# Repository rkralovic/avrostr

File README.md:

# AVR-OSTR

This project is an implementation of a turtle robot based on AVR microcontroller.

## Mechanical design

The hardware design is based on [https://www.instructables.com/OSTR/](https://www.instructables.com/OSTR/).

Mechanical parts are designed using [OpenSCAD](https://openscad.org). Running
`make` in the `mechanical` directory builds STL files suitable for 3d-printing.
The design has the following parts:

* `Chassis.scad` is the main chassis structure.
* `Caster.scad` holds a support bearing ball.
* `PenCollar.scad` holds the pen.
* `Wheel.scad` is the wheel. You need to print 2 of them

The following extra parts are needed for assembly:

* Bearing ball with diameter approx 15.875mm.
* 2x o-ring 42mm x 3mm used as tires. It is important that it fits tightly to the wheels.
* 2x battery holder for 2 AA batteries (e.g. 12BHC321A-GR).
* M3 nuts and screws (for battery holders and stepper motors).
* DIN7981 screws to fix the wheels and PCB
  ([example](https://www.conrad.ch/de/p/toolcraft-din7981-c-h-2-9c4-5-linsenblechschrauben-2-9-mm-4-5-mm-kreuzschlitz-phillips-din-7981-stahl-verzinkt-1-st-889176.html?searchType=SearchRedirect)).
* (optional) Two large nuts that can be glued to the back of the chassis for better stability.

## Electronic design

Schematics and PCB layout are provided as a Kicad project in this directory.
Component list is summarized in `bom.csv`.

## Firmware

Source of the firmware, which runs on the AVR microcontroller of the robot, is
in the directory `fw`. You need reasonable new avr-g++ in order to compile the
firmware, which uses C++20. Development was done using avr-g++ 11.2.0.

The AVR firmware can be flashed using avrdude and an UPDI-capable programmer by
running `make write`.

A smoke test is in `fw/test`. It uses simavr library to simulate the AVR code.

Note: To compile the firmware, you need to first generate the input data, see
the next section for details. Beyond that, the tests depend on simavr, gmock,
and gtest libraries.

## Image data

The image data for the robot are prepared using a tool in `gendata` directory.
Source images are in `gendata/input` in svg file format. The tool depend on
absl, cairo, xcb, cairo-pdf, and xcb-iccm libraries.

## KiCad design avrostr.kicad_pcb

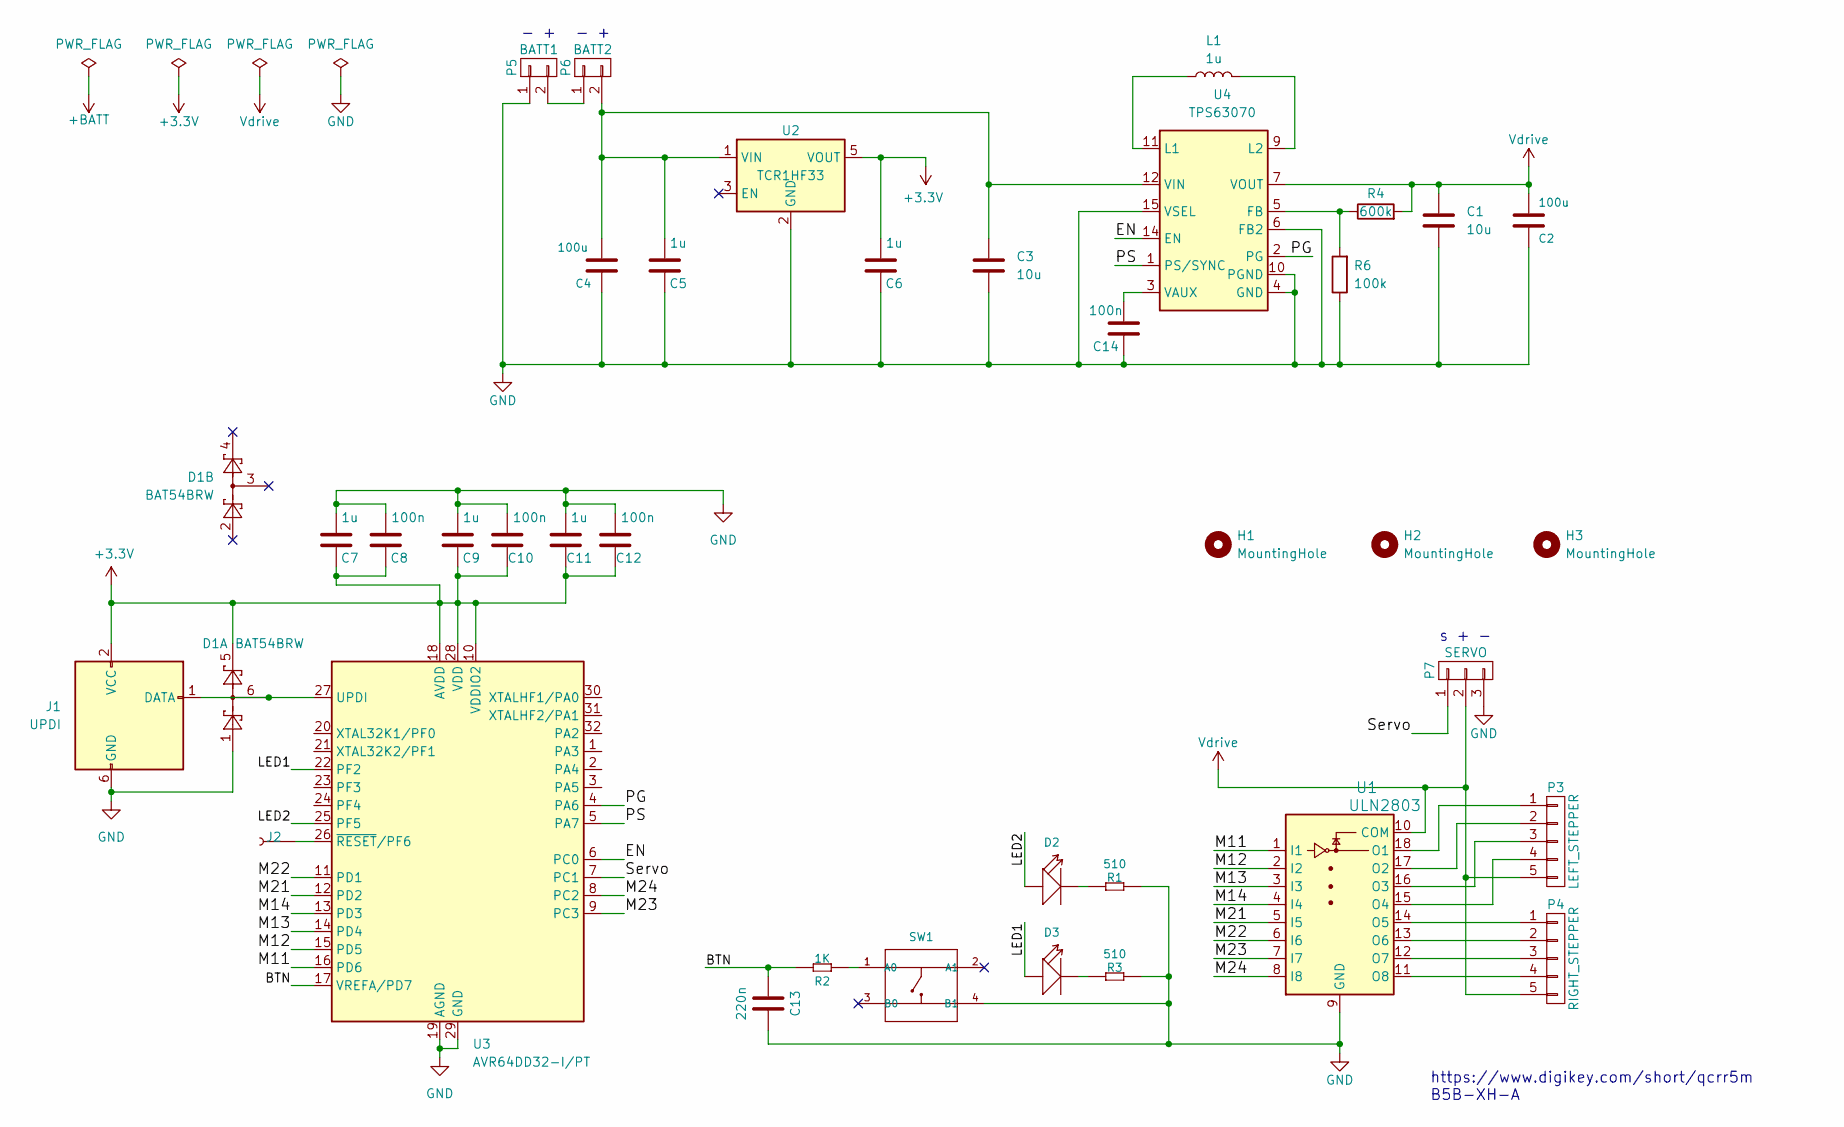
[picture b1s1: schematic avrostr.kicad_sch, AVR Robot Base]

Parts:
C1, C3: 10u; C_0402_1005Metric; Mouser 81-GRM155R61A106ME1D
C2, C4: 100u; C_1210_3225Metric; Mouser 81-GRM32ER61A107ME0K
C5, C6, C7, C9, C11: 1u; C_0402_1005Metric; Mouser 81-GRM155R61H105ME5D
C8, C10, C12, C14: 100n; C_0402_1005Metric; Mouser 81-GRM155R71H104KE4D
C13: 220n; C_0603_1608Metric; Mouser GCM188R71H224KA64
D1: BAT54BRW; SOT-363_SC-70-6; Mouser 241-BAT54BRWR100001
D2, D3: RED; LED_0603_1608Metric; Mouser 710-150060RS75000
H1, H2, H3: MountingHole; MountingHole_3.2mm_M3_ISO14580
J1: UPDI; PinHeader_2x03_P2.54mm_Vertical; Mouser 649-78511-203HLF
J2: Conn_01x01_Female; TestPoint_Pad_D1.0mm
L1: 1u; L_Coilcraft_XxL4020; Mouser XFL4020-102MEC
P3: LEFT_STEPPER; JST_B5B-XH-A; Digikey 455-2270-ND
P4: RIGHT_STEPPER; JST_B5B-XH-A; Digikey 455-2270-ND
P5: BATT1; TerminalBlock_Phoenix_PT-1,5-2-3.5-H_1x02_P3.50mm_Horizontal; Mouser 651-1984617
P6: BATT2; TerminalBlock_Phoenix_PT-1,5-2-3.5-H_1x02_P3.50mm_Horizontal; Mouser 651-1984617
P7: SERVO; Pin_Header_Straight_1x03; Digikey 1849-1003-ND
R1, R3: 510; R_0402_1005Metric; Mouser 603-RC0402FR-13510RL
R2: 1K; R_0402_1005Metric; Mouser 603-AC0402FR-071KL
R4: 600k; R_0402_1005Metric; Mouser RC0402FR-07604KL
R6: 100k; R_0402_1005Metric; Mouser 791-WR04X1003FTL
SW1: type="R" model="SMD-BUTTON_4P-5.2X5.2X1.5MM-SKQGA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; SW4-SMD-5.2X5.2X1.5MM; MPN SKQGADE010; LCSC C318889
U1: ULN2803; SOP-18_7x12.5mm_P1.27mm; Digikey 4518-ULN2803ACT-ND
U2: TCR1HF33; SOT-23-5; Mouser 757-TCR1HF33BLMCT
U3: AVR64DD32-I/PT; TQFP-32_7x7mm_P0.8mm; Digikey 150-AVR64DD32-I/PT-ND
U4: TPS63070; VQFN-15-TPS63070; Mouser 595-TPS630702RNMR

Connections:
+3.3V: C6.2, C7.1, C8.2, C9.1, C10.2, C11.1, C12.2, D1.5, J1.2 (VCC), U2.5 (VOUT), U3.10 (VDDIO2), U3.18 (AVDD), U3.28 (VDD)
/BTN: C13.1, R2.1, U3.17 (VREFA/PD7)
/EN: U3.6 (PC0), U4.14 (EN)
/LED1: D3.1 (+), U3.22 (PF2)
/LED2: D2.1 (+), U3.25 (PF5)
/M11: U1.1 (I1), U3.16 (PD6)
/M12: U1.2 (I2), U3.15 (PD5)
/M13: U1.3 (I3), U3.14 (PD4)
/M14: U1.4 (I4), U3.13 (PD3)
/M21: U1.5 (I5), U3.12 (PD2)
/M22: U1.6 (I6), U3.11 (PD1)
/M23: U1.7 (I7), U3.9 (PC3)
/M24: U1.8 (I8), U3.8 (PC2)
/PG: U3.4 (PA6), U4.2 (PG)
/PS: U3.5 (PA7), U4.1 (PS/SYNC)
/Servo: P7.1, U3.7 (PC1)
GND: C1.2, C2.2, C3.2, C4.2, C5.1, C6.1, C7.2, C8.1, C9.2, C10.1, C11.2, C12.1, C13.2, C14.2, D1.1, J1.6 (GND), P5.1, P7.3, R1.2, R3.2, R6.1, SW1.4 (B1), U1.9 (GND), U2.2 (GND), U3.19 (AGND), U3.29 (GND), U4.4 (GND), U4.6 (FB2), U4.10 (PGND), U4.15 (VSEL)
unnamed: C14.1, U4.3 (VAUX)
unnamed: D1.6, J1.1 (DATA), U3.27 (UPDI)
unnamed: D2.2 (-), R1.1
unnamed: D3.2 (-), R3.1
unnamed: J2.1, U3.26 (~RESET/PF6)
unnamed: L1.1, U4.11 (L1)
unnamed: L1.2, U4.9 (L2)
unnamed: P3.1, U1.18 (O1)
unnamed: P3.2, U1.17 (O2)
unnamed: P3.3, U1.16 (O3)
unnamed: P3.4, U1.15 (O4)
unnamed: P4.1, U1.14 (O5)
unnamed: P4.2, U1.13 (O6)
unnamed: P4.3, U1.12 (O7)
unnamed: P4.4, U1.11 (O8)
unnamed: P5.2, P6.1
unnamed: R2.2, SW1.1 (A0)
unnamed: R4.1, R6.2, U4.5 (FB)
VIN: C3.1, C4.1, C5.2, P6.2, U2.1 (VIN), U4.12 (VIN), U4.12_13 (VIN), U4.13 (VIN)
Vdrive: C1.1, C2.1, P3.5, P4.5, P7.2, R4.2, U1.10 (COM), U4.7 (VOUT), U4.7_8 (VOUT), U4.8 (VOUT)

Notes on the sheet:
s + -
- +
https://www.digikey.com/short/qcrr5m B5B-XH-A

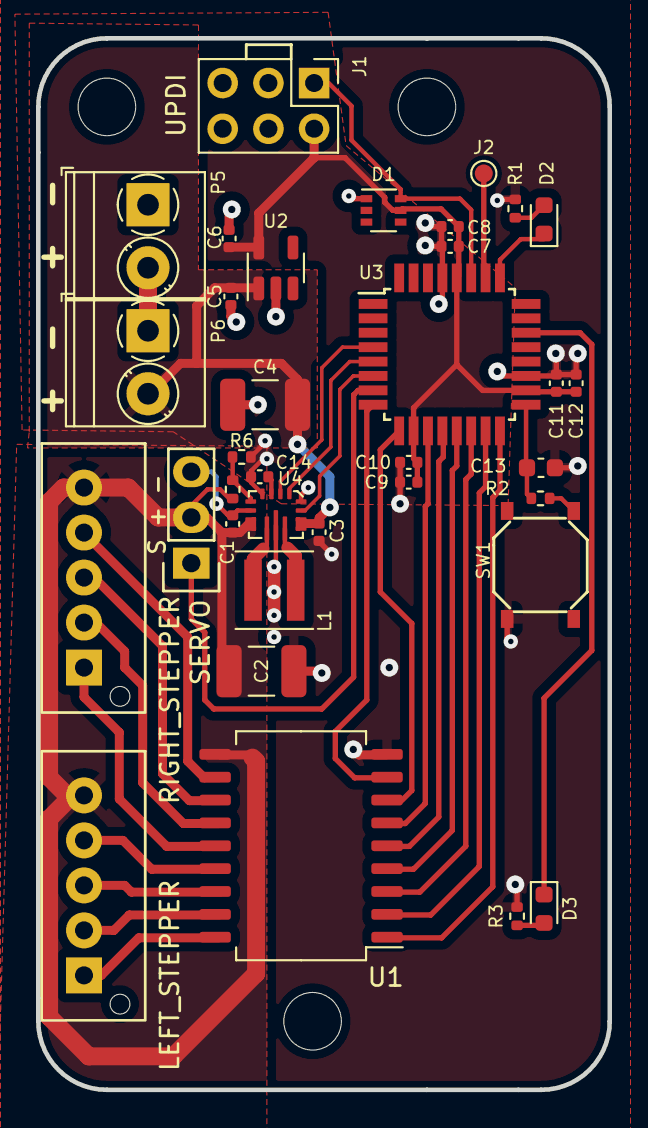
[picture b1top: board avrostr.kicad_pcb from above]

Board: 2 copper layers, 31.7 x 58.4 mm, 38 parts (0 on the bottom side), 37 nets.

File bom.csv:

Part number,Quantity,Designators,Footprint,Value
81-GRM155R61A106ME1D,2,"C1,C3",Capacitor_SMD:C_0402_1005Metric,10u
81-GRM32ER61A107ME0K,2,"C2,C4",riso:C_1210_3225Metric,100u
81-GRM155R61H105ME5D,5,"C5,C6,C7,C9,C11",Capacitor_SMD:C_0402_1005Metric,1u
81-GRM155R71H104KE4D,4,"C8,C10,C12,C14",Capacitor_SMD:C_0402_1005Metric,100n
GCM188R71H224KA64,1,C13,Capacitor_SMD:C_0603_1608Metric,220n
241-BAT54BRWR100001,1,D1,Package_TO_SOT_SMD:SOT-363_SC-70-6,BAT54BRW
710-150060RS75000,2,"D2,D3",LED_SMD:LED_0603_1608Metric,RED
649-78511-203HLF,1,J1,Connector_PinHeader_2.54mm:PinHeader_2x03_P2.54mm_Vertical,UPDI
XFL4020-102MEC,1,L1,Inductor_SMD:L_Coilcraft_XxL4020,1u
651-1984617,2,"P5,P6","TerminalBlock_Phoenix:TerminalBlock_Phoenix_PT-1,5-2-3.5-H_1x02_P3.50mm_Horizontal",BATT1
538-22-28-9034,1,P7,library:Pin_Header_Straight_1x03,SERVO
603-RC0402FR-13510RL,2,"R1,R3",Resistor_SMD:R_0402_1005Metric,510
603-AC0402FR-071KL,1,R2,Resistor_SMD:R_0402_1005Metric,1K
RC0402FR-07604KL,1,R4,Resistor_SMD:R_0402_1005Metric,600k
791-WR04X1003FTL,1,R6,Resistor_SMD:R_0402_1005Metric,100k
611-PTS526SM15SMTR2L,1,SW1,riso:SW4-SMD-5.2X5.2X1.5MM,SMD-BUTTON_4P-5.2X5.2X1.5MM-SKQGADE010_
757-TCR1HF33BLMCT,1,U2,Package_TO_SOT_SMD:SOT-23-5,TCR1HF33
494-AVR64DD32-I/PT,1,U3,Package_QFP:TQFP-32_7x7mm_P0.8mm,AVR64DD32-I/PT
595-TPS630702RNMR,1,U4,riso:VQFN-15-TPS63070,TPS63070
932-MIKROE-1530,2,"P3,P4",library:JST_B5B-XH-A,LEFT_STEPPER
12BHC321A-GR,2,"P5,P6","TerminalBlock_Phoenix:TerminalBlock_Phoenix_PT-1,5-2-3.5-H_1x02_P3.50mm_Horizontal",BATT1
485-169,1,P7,library:Pin_Header_Straight_1x03,SERVO
4518-ULN2803ACT-ND,1,U1,Package_SO:SOP-18_7x12.5mm_P1.27mm,ULN2803

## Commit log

2024-07-04 Update README.md - fix image link
